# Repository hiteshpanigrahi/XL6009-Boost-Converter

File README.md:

# 🔋 XL6009 Boost Converter – Custom PCB Design

## 📘 Project Overview

This is a **custom-designed DC-DC boost converter** PCB built around the **XL6009** switching regulator IC. It’s capable of efficiently stepping up voltage from as low as **5V up to 32V**, delivering up to **4A of output current** with up to **94% efficiency**.

The converter is compact and optimized for applications in **IoT, embedded systems, robotics**, and other projects requiring reliable power delivery.

---

## ⚙️ About the XL6009

The **XL6009** is a monolithic **high-frequency PWM step-up (boost) regulator** from XLSEMI. It’s widely used as a drop-in replacement for the LM2577 but with improved performance and efficiency.

### 🔑 Key Specifications:
- **Input Voltage Range:** 3.6V to 32V  
- **Output Voltage Range:** 5V to 35V (adjustable)  
- **Output Current:** Up to 4A  
- **Switching Frequency:** 400 kHz  
- **Efficiency:** Up to 94%  
- **Integrated MOSFET switch** and internal compensation  
- Built-in soft start and thermal shutdown

---

## ✅ Design Highlights

- 🔧 **Custom 2-layer PCB** designed in **KiCAD**
- 🌀 **Optimized switching loop layout** for reduced EMI and noise
- 🔥 **Thick power traces** and **thermal relief pads** for heat handling
- 🛡️ Full **GND pour** for improved grounding and stability
- 📐 **DRC/ERC clean** and ready for fabrication
- 📦 Includes **BOM, Schematic, and Gerber files**

---

## 📚 What I Learned

Working on this project gave me practical experience in:

- 💡 Designing **switch-mode power supplies (SMPS)**  
- 🧰 Using **KiCAD** for professional PCB design  
- ⚡ Understanding **power trace width, component placement**, and **loop area minimization**  
- 🧠 Making design decisions based on **datasheet parameters** and performance goals  
- 🧪 Preparing a project for real-world fabrication and testing

---

## 🖼️ Gallery

| 3D Render | Layout Snapshot | Schematic Snapshot |
|:-------------:|:---------:|:---------------:|
|  |  |  |

---

## 🛠️ How to Use

1. Connect your input voltage (5V–32V) to the `VIN` and `GND` terminals.
2. Adjust the onboard potentiometer to set your desired output voltage.
3. Measure the output voltage at `VOUT` and `GND`.
4. Use a heatsink if operating at high currents or continuous load.

---

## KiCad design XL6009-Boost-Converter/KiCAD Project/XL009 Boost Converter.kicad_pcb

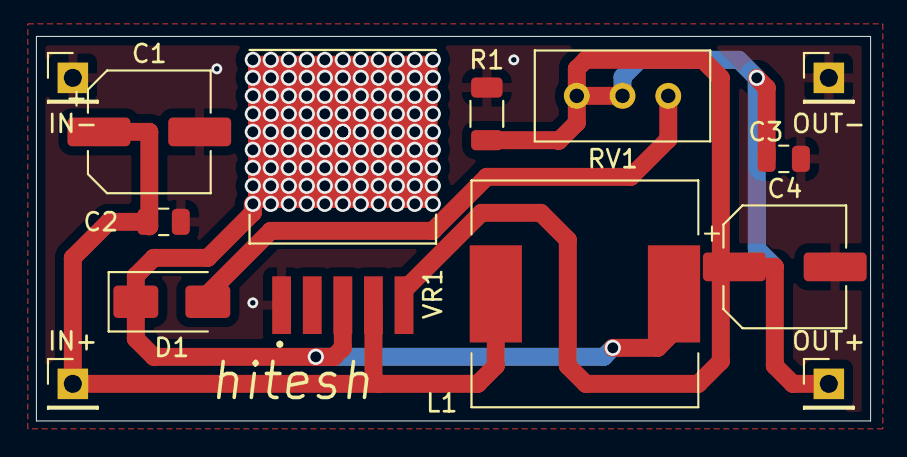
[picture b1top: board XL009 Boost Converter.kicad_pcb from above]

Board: 2 copper layers, 46.3 x 21.4 mm, 13 parts (0 on the bottom side), 5 nets.

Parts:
C1: 47uF/50V; CP_Elec_6.3x5.4
C2, C3: 1uF; C_0805_2012Metric
C4: 220uF/50V; CP_Elec_6.3x5.4
D1: SS34; D_SMA
IN+: Conn_01x01_Pin; PinHeader_1x01_P2.54mm_Vertical
IN-: Conn_01x01_Pin; PinHeader_1x01_P2.54mm_Vertical
L1: 33uH; L_12x12mm_H8mm
OUT+: Conn_01x01_Pin; PinHeader_1x01_P2.54mm_Vertical
OUT-: Conn_01x01_Pin; PinHeader_1x01_P2.54mm_Vertical
R1: 1K; R_1206_3216Metric
RV1: 50K; Potentiometer_Bourns_3296W_Vertical
VR1: XL6009; DPAK170P1435X465-6N

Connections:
GND: C1.2, C2.2, C3.2, C4.2, IN-.1, OUT-.1, R1.2, VR1.1 (GND)
unnamed: D1.2 (A), RV1.1
unnamed: D1.1 (K), L1.2, VR1.3 (SW), VR1.6 (SW)
unnamed: C3.1, C4.1, OUT+.1, R1.1, RV1.2, RV1.3, VR1.5 (FB)
unnamed: C1.1, C2.1, IN+.1, L1.1, VR1.4 (VIN)

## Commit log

2025-06-02 Rename PCB Layout.png to PCB_Layout.png
2025-06-02 Rename XL009 Boost Converter.csv to BOM.csv
